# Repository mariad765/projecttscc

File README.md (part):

# projecttscc
date: 2025

# Proiect: OpenBook
Acest proiect utilizează Autodesk Fusion 360 pentru realizarea designului carcasei și a plăcii PCB pentru OpenBook, având la bază microcontrollerul ESP32-C6. Include senzori, module de alimentare și componente conectate prin diverse interfețe.

# Diagrama Bloc

### General:
```
+------------------------+     +------------------------+     +------------------------+
| USB-C + ESD Protection | --> | LDO Voltage Regulator  | --> | Li-Po Charging Ctrl.   |
+------------------------+     +------------------------+     +------------------------+
                                                            |
                                                            v
                                                      +----------------+
                                                      |   Battery      |
                                                      | (3.7V Li-Po)   |
                                                      +----------------+
                                                            |
                                                            v
+------------------+     +------------------+         +-------------------+
| RTC DS3231SN     |<--->|   ESP32-C6       |<------->| E-Paper Display   |
+------------------+     +------------------+         | (Header + Driver) |
                           ^    ^   ^   ^              +-------------------+
                           |    |   |   |
       +------------------+    |   |   +--------------------+
       |                       |   |                        |
       v                       v   v                        v
+--------------+       +--------------+           +----------------------+
| SD Card Slot |       | BME688 Sensor|           | External Flash 64MB  |
+--------------+       +--------------+           +----------------------+
                           ^   |
                           |   v
               +-----------------------------+
               | Voltage Supervisor + Reset  |
               | Boot / IO Button Module     |
               +-----------------------------+

                           ^
                           |
                    +-------------+
                    | EPD Power   |
                    +-------------+

                           ^
                           |
              +-----------------------+
              | SPI ESD Protection    |
              +-----------------------+

                           ^
                           |
            +--------------------------+
            | Qwic / Stemma QT Header |
            +--------------------------+

                           ^
                           |
                     +-----------+
                     | Test Pads |
                     +-----------+

```

### Organizarea componentelor mici:
```

                        +------------------------+
                        | USB-C + ESD Protection |
                        | R1, F1, D1             |
                        +-----------+------------+
                                    |
                                    v
                      +-----------------------------+
                      | LDO Voltage Regulator       |
                      | U4 (XC6220)                 |
                      | D2 (Schottky)               |
                      | C1, C2 (Capacitors)         |
                      +-----------+-----------------+
                                  |
                                  v
          +----------------------------------------------+
          | Li-Po Charging Controller (MCP73831)         |
          | RPROG, C1_BAT, C2_BAT                        |
          +--------------------+-------------------------+
                               |
                               v
                          +---------+
                          | Battery |
                          +---------+

          +------------------------------------------+
          |                ESP32-C6                  |
          | U2, conectat cu GPIO la toate modulele   |
          +--+--------+----------+----------+--------+
             |        |          |          |
             |        |          |          |
             |        |          |          |
             v        v          v          v
+------------------+ +------------------+ +-------------------+ +-------------------+
| RTC DS3231SN     | | BME688 Sensor    | | E-Paper Display   | | External NOR Flash|
| U3, C1, C2       | | Ux, Cx (Filter)  | | Header + Drive    | | U1, Cx (Decouple) |
| + CRYSTAL        | | R (Pull-ups)     | | Q3 (MOSFET),      | |                   |
+------------------+ +------------------+ | L1 (Inductor),    | +-------------------+
                                          | D3, D4 (Diodes)   |
                                          | C3, C4, C5, C6    |
                                          +-------------------+

                      +------------------------------------+
                      | SD Card Module (SPI)              |
                      | + Pull-up Resistors               |
                      +------------------------------------+
                      +--------------------------------------------+
                      | Voltage Supervisor + Boot + Reset Buttons  |
                      | Ux (BD52), R1, R2, C1, C2                   |
                      +--------------------------------------------+
                      +------------------+ +--------------------+
                      | EPD Power        | | SPI ESD Protection |
                      | Zener Diode      | | TVS Diodes         |
                      +------------------+ +--------------------+
                      +---------------------------+
                      | Qwiic / Stemma QT Header  |
                      | 4-Pin Connector           |
                      +---------------------------+

                      +---------------------------+
                      | Test Pads (TP1 - TP17)    |
                      +---------------------------+

```

#### Legenda componente:
R = Rezistențe (pull-up, pull-down, programare)

C = Condensatori (filtrare, decuplare, bypass)

D = Diode (Schottky, Zener, TVS)

Q = Tranzistori (MOSFET, BJT)

L = Bobine (inductoare pentru EPD)

U = Integrate (ESP32-C6, MCP73831, etc.)

TP = Test Pads

CRYSTAL = Oscilator 32.768kHz pentru RTC

<prev>

| **Device**                             | **Datasheet**                                                                                       | **Purchase URL**                                                                                                                                               | **Notes**                                                                                                                                                                                                                                                                                                                |
|----------------------------------------|----------------------------------------------------------------------------------------------------|---------------------------------------------------------------------------------------------------------------------------------------------------------------|--------------------------------------------------------------------------------------------------------------------------------------------------------------------------------------------------------------------------------------------------------------------------------------------------------------------------|
| ADAFRUIT_LEDCHIP-LED0603               | [Datasheet](https://dammedia.osram.info/media/resource/hires/osram-dam-5178061/LH%20R974_EN.pdf)   | [Purchase](https://eu.mouser.com/ProductDetail/ams-OSRAM/LH-R974?qs=rUek3o0zKEvmwAoLLbCfCQ%3D%3D)                                                              |                                                                                                                                                                                                                                                                                                                          |
| ESP32_WROVER_EAGLE-LTSPICE_RR0402      | [Datasheet](https://eu.mouser.com/datasheet/2/447/PYu_RT_1_to_0_01_RoHS_L_15-3461507.pdf)           | [Purchase](https://eu.mouser.com/ProductDetail/YAGEO/RT0402BRE072KL?qs=gY0y7AQI9SOEMRqvTCljCA%3D%3D)                                                           |                                                                                                                                                                                                                                                                                                                          |
| ESP32_WROVER_EAGLE-LTSPICE_RR0402      | [Datasheet](https://eu.mouser.com/datasheet/2/447/PYu_SR_20105_RoHS_L_12-3461462.pdf)               | [Purchase](https://eu.mouser.com/ProductDetail/YAGEO/SR0402FR-0710KL?qs=TyBUSTk9pD%2F02BJ2PplVgA%3D%3D)                                                       |                                                                                                                                                                                                                                                                                                                          |
| EAGLE-LTSPICE_CC0402                   | [Datasheet](https://eu.mouser.com/datasheet/2/447/KEM_C1003_C0G_SMD-3316496.pdf)                    | [Purchase](https://eu.mouser.com/ProductDetail/KEMET/C0402C100J4GACTU?qs=mjekseImwbbdX0mMb15eGA%3D%3D)                                                          |                                                                                                                                                                                                                                                                                                                          |
| SJ                                     | [Datasheet](https://www.snapeda.com/parts/5112/Keystone%20Electronics/datasheet/)                    | [Purchase](https://eu.mouser.com/ProductDetail/Keystone-Electronics/5112?utm_campaign=mouser&qs=u16ybLDytRZh2kbiE9WIqQ==&utm_medium=online&utm_source=snapedaonline&utm_content=datasheet) |                                                                                                                                                                                                                                                                                                                          |
| ESP32_WROVER_EAGLE-LTSPICE_RR0402      | [Datasheet](https://eu.mouser.com/datasheet/2/447/PYu_RC_Group_51_RoHS_L_12-3368608.pdf)            | [Purchase](https://eu.mouser.com/ProductDetail/YAGEO/RC0402FR-07226RL?qs=ZELcmBmapfyYDZKSOq20kw%3D%3D)                                                           |                                                                                                                                                                                                                                                                                                                          |
| EAGLE-LTSPICE_CC0402                   | [Datasheet](https://eu.mouser.com/datasheet/2/447/KEM_C1018_X7R_SnPb_SMD-3316276.pdf)               | [Purchase](https://eu.mouser.com/ProductDetail/KEMET/C0402C104K4RAL?qs=pIZUS6sqCWCaMuP2QVR%2Fog%3D%3D&srsltid=AfmBOorFGwDGmQ6lWmC_Jiog7gZnCk6L84apRuEeDYw4gmpryDUgmfwW)              |                                                                                                                                                                                                                                                                                                                          |
| ESP32_WROVER_EAGLE-LTSPICE_CC0402      | [Datasheet](https://eu.mouser.com/datasheet/2/447/KEM_C1002_X7R_SMD-3316098.pdf)                    | [Purchase](https://eu.mouser.com/ProductDetail/KEMET/C0402C104K4RAC?qs=sykUljcfnH1GXndxGT8AHQ%3D%3D)                                                           |                                                                                                                                                                                                                                                                                                                          |
| RCL_CPOL-EUCT3528                      | [Datasheet](https://www.snapeda.com/parts/OF-SMD3528WC/Optoflash/datasheet/)                          | [Purchase](https://www.tme.eu/en/details/of-smd3528wc/smd-white-leds/optoflash/)                                                                                  |                                                                                                                                                                                                                                                                                                                          |
| ESP32_WROVER_EAGLE-LTSPICE_CC0402      | [Datasheet](https://eu.mouser.com/datasheet/2/447/KEM_C1018_X7R_SnPb_SMD-3316276.pdf)               | [Purchase](https://eu.mouser.com/ProductDetail/KEMET/C0402C104K4RAL?qs=pIZUS6sqCWCaMuP2QVR%2Fog%3D%3D)                                                           |                                                                                                                                                                                                                                                                                                                          |
| 112A-TAAR-R03_ATTEND                   | [Datasheet](https://www.snapeda.com/parts/112A-TAAR-R03/Attend/datasheet/)                            | [Purchase](https://www.tme.eu/ro/details/mcc-sdmicro/conectori-pentru-cartele/attend/112a-taar-r03/)                                                              |                                                                                                                                                                                                                                                                                                                          |
| EAGLE-LTSPICE_CC0402                   | [Datasheet](https://eu.mouser.com/datasheet/2/447/KEM_C1006_X5R_SMD-3316465.pdf)                    | [Purchase](https://eu.mouser.com/ProductDetail/KEMET/C0402C475M9PAC7411?qs=cpo3%2FpBou2jRzZxyxJnMGg%3D%3D)                                                          |                                                                                                                                                                                                                                                                                                                          |
| ESP32_WROVER_SPARKFUN-DISCRETESEMI_MOSFET_PCH-DMG2305UX-7 | [Datasheet](https://www.diodes.com/assets/Datasheets/DMG2305UX.pdf) | [Purchase](https://eu.mouser.com/ProductDetail/Diodes-Incorporated/DMG2305UX-7?qs=L1DZKBg7t5F%2FNBHrjfxC%252Bg%3D%3D) |                                                                                                                                                                                                                                                                                                                          |
| 744043680IND_4828-WE-TPC_WRE           | [Datasheet](https://www.we-online.com/components/products/datasheet/744043680.pdf)                  | [Purchase](https://eu.mouser.com/ProductDetail/Wurth-Elektronik/744043680?qs=PGXP4M47uW6VkZq%252BkzjrHA%3D%3D)                                                    |                                                                                                                                                                                                                                                                                                                          |
| BD5229G-TR                             | [Datasheet](https://fscdn.rohm.com/en/products/databook/datasheet/ic/power/voltage_detector/bd52xxg-e.pdf) | [Purchase](https://eu.mouser.com/ProductDetail/ROHM-Semiconductor/BD5229G-TR?qs=4kLU8WoGk0vvnhrrYwdszw%3D%3D) |                                                                                                                                                                                                                                                                                                                          |
| ESP32_WROVER_BME680_BME680             | [Datasheet](https://eu.mouser.com/datasheet/2/783/bst_bme688_fl000-2307034.pdf)                      | [Purchase](https://eu.mouser.com/ProductDetail/Bosch-Sensortec/BME688?qs=IS%252B4QmGtzzqQoVDscqwx3A%3D%3D)                                                       |                                                                                                                                                                                                                                                                                                                          |
| BUTTON_CUSYOMV1                         | [Datasheet](https://www.ckswitches.com/media/1482/kms.pdf)                                           | [Purchase](https://eu.mouser.com/ProductDetail/CK/KMS231G?qs=cygERTaPE9Aulmq4rq4WXQ%3D%3D)                     | [see note 1]                                                                                      |
| CPH3225A                               | [Datasheet](https://eu.mouser.com/datasheet/2/360/Seiko_Instruments_MicroBattery_E_20230330_2024Jan_-3561061.pdf) | [Purchase](https://eu.mouser.com/ProductDetail/Seiko-Semiconductors/CPH3225A?qs=3etwrb1wR%252BhUOph6lAO7eg%3D%3D&utm_id=6470900573&utm_source=google&utm_medium=cpc&utm_marketing_tactic=emeacorp&gad_source=1&gclid=CjwKCAjwzMi_BhACEiwAX4YZUD6usznTzJWXm4Z9u8rBBFy2NakSyAr25YMlMpxMyBTQ3bVXFg2nFhoCpx0QAvD_BwE) |                                                                                                                                                                                                                                                                                                                          |
| DS3231SN#                              | [Datasheet](https://eu.mouser.com/datasheet/2/609/DS3231-3421123.pdf)                                | [Purchase](https://www.snapeda.com/api/url_track_click_mouser/?unipart_id=562593&manufacturer=Seiko%20Instruments&part_name=CPH3225A&search_term=None)          |                                                                                                                                                                                                                                                                                                                          |
| ESP32-C6-WROOM-1-N8                    | [Datasheet](https://eu.mouser.com/datasheet/2/891/Espressif_ESP32_C6_WROOM_1__Datasheet_V0_1_PRELIMI-3239987.pdf) | [Purchase](https://eu.mouser.com/ProductDetail/Espressif-Systems/ESP32-C6-WROOM-1-N8?qs=8Wlm6%252BaMh8ST02Gmwp74cw%3D%3D)                                            |                                                                                                                                                                                                                                                                                                                          |
| ESP32C6_VARISTORCN1812                 | [Datasheet](https://www.snapeda.com/parts/PFMF.050.2/Schurter/datasheet/)                             | [Purchase](https://www.digikey.com/en/products/detail/schurter-inc/PFMF-050-2/1731348?utm_campaign=buynow&utm_medium=aggregator&utm_source=snapeda)               |                                                                                                                                                                                                                                                                                                                          |
| ESP32_WROVER_AVX---SD0805S020S1R0_AVX_SD0805S020S1R0_0_0AVX_SD0805S020S1R0_0_0 | [Datasheet](http://datasheets.avx.com/schottky.pdf) | [Purchase](https://www.kyocera-avx.com/products/diodes/lead-less-chip-schottky-barrier-diodes/)               |                                                                                                                                                                                                                                                                                                                          |
| ESP32_WROVER_SPARKFUN-IC-POWER_MCP73831 | [Datasheet](https://eu.mouser.com/datasheet/2/268/MCP73831_Family_Data_Sheet_DS20001984H-3441711.pdf) | [Purchase](https://eu.mouser.com/ProductDetail/Microchip-Technology/MCP73831T-2ACI-OT?qs=yUQqVecv4qvbBQBGbHx0Mw%3D%3D)               |                                                                                                                                                                                                                                                                                                                          |
| FH34SRJ-24S-0.5SH_99_                  | [Datasheet](https://www.snapeda.com/parts/FH34SRJ-24S-0.5SH(99)/Hirose%20Electric/datasheet/)         | [Purchase](https://www.digikey.com/en/products/detail/hirose-electric-co-ltd/FH34SRJ-24S-0-5SH-99/5132529?utm_campaign=buynow&utm_medium=aggregator&utm_source=snapeda) |                                                                                                                                                                                                                                                                                                                          |
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
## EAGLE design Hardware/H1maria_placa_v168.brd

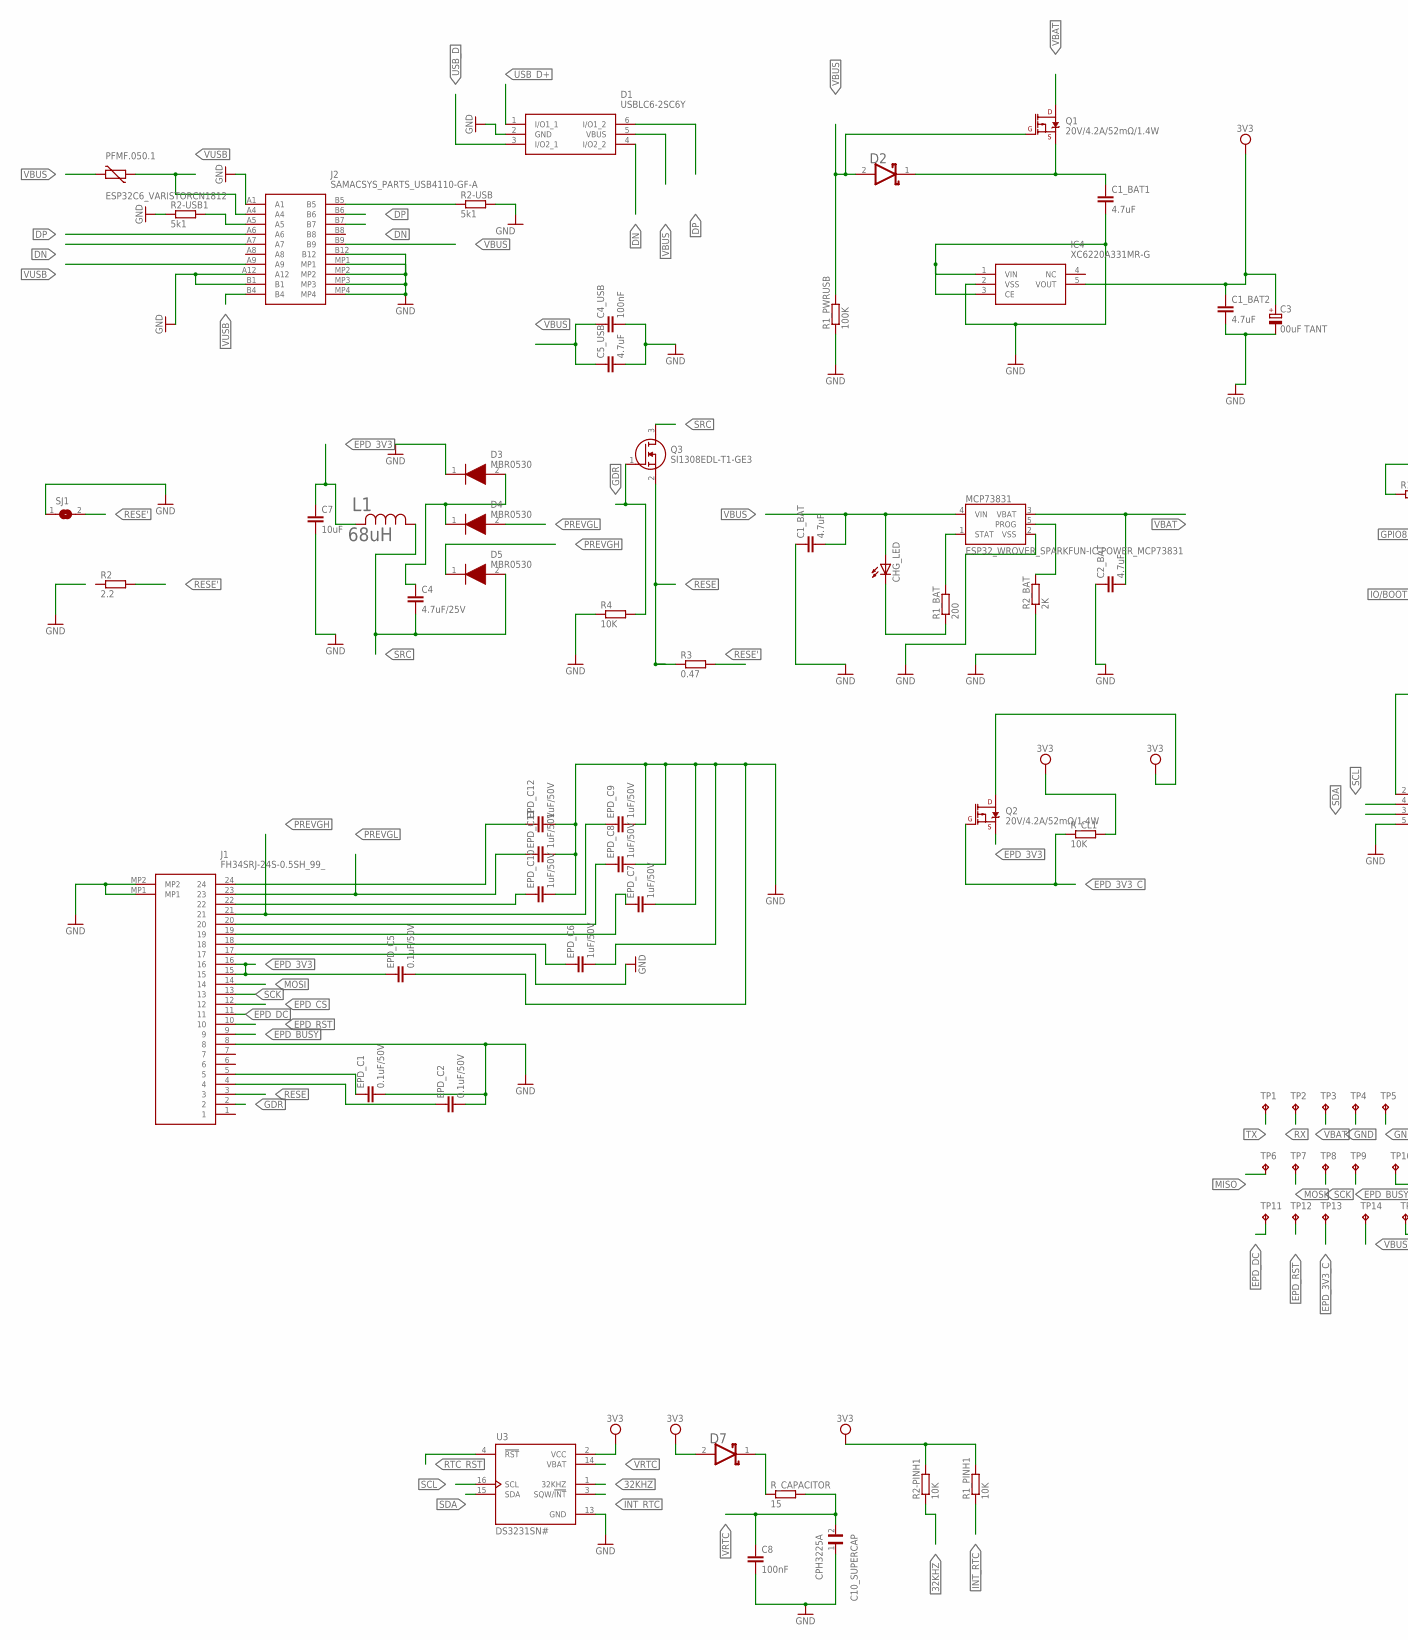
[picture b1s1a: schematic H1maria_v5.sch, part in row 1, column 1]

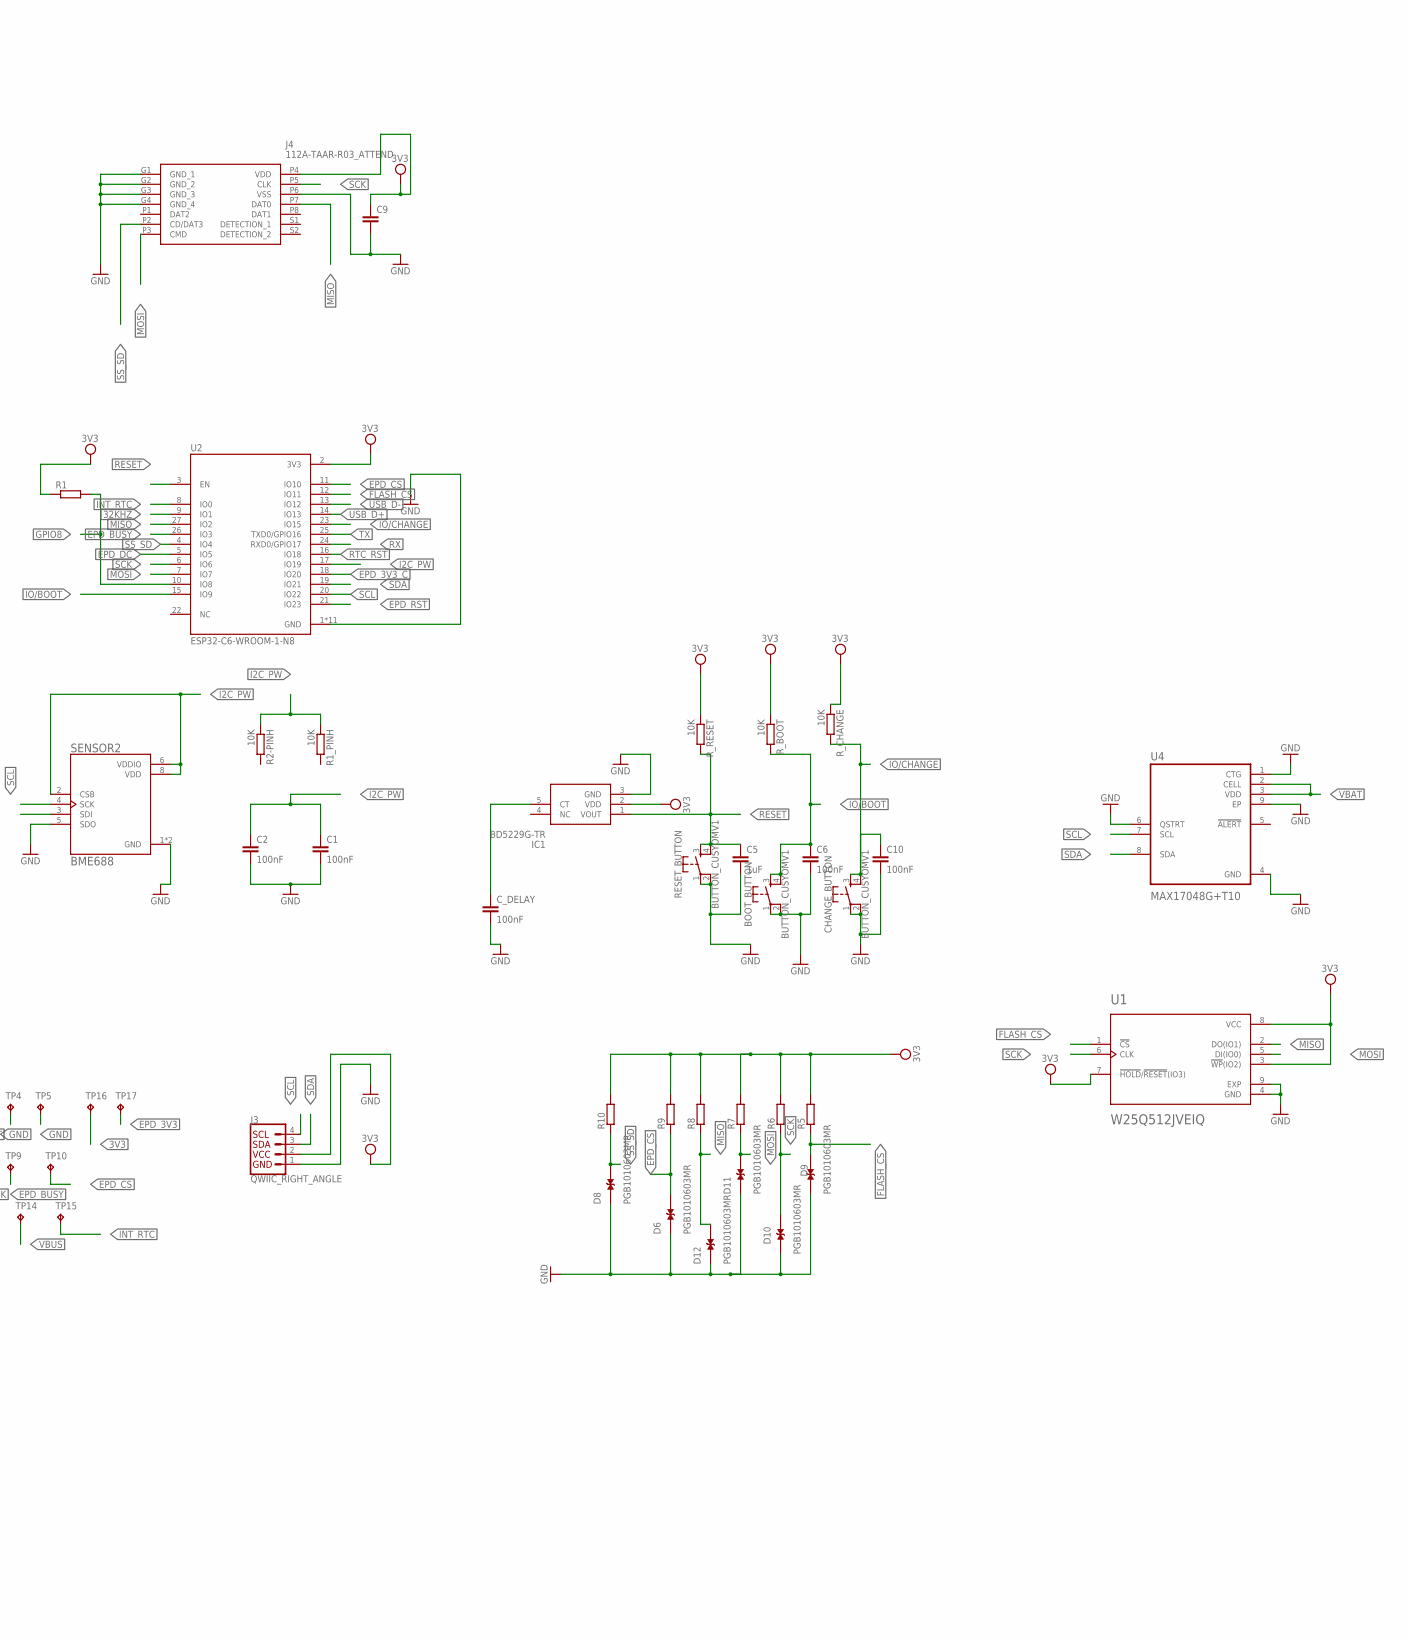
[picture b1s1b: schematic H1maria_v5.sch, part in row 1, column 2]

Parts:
BOOT_BUTTON: BUTTON_CUSYOMV1; MYBUTTON
C1, C2: 100nF; ESP32_WROVER_EAGLE-LTSPICE_C0402
C1_BAT, C1_BAT1, C1_BAT2, C2_BAT, C5_USB: 4.7uF; EAGLE-LTSPICE_C0402
C3: 00uF TANT; RCL_CT3528
C4: 4.7uF/25V; ESP32_WROVER_EAGLE-LTSPICE_C0402
C4_USB, C6, C8, C10: 100nF; EAGLE-LTSPICE_C0402
C5: 1uF; EAGLE-LTSPICE_C0402
C7: 10uF; ESP32_WROVER_EAGLE-LTSPICE_C0402
C9: ESP32_WROVER_EAGLE-LTSPICE_CC0402; ESP32_WROVER_EAGLE-LTSPICE_C0402
C10_SUPERCAP: CPH3225A; CAPCP3225X100N
CHANGE_BUTTON: BUTTON_CUSYOMV1; MYBUTTON
CHG_LED: ADAFRUIT_LEDCHIP-LED0603; ADAFRUIT_CHIP-LED0603
C_DELAY: 100nF; EAGLE-LTSPICE_C0402
D1: USBLC6-2SC6Y; SOT95P280X145-6N
D2: SD0805S020S1R0; ESP32_WROVER_AVX---SD0805S020S1R0_AVX_SD0805S020S1R0_0
D3, D4, D5: MBR0530; SOD3716X135N
D6, D8, D9, D10, D11, D12: PGB1010603MR; DIOC1608X36N
D7: ESP32_WROVER_AVX---SD0805S020S1R0_AVX_SD0805S020S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; ESP32_WROVER_AVX---SD0805S020S1R0_AVX_SD0805S020S1R0_0
EPD_C1, EPD_C2, EPD_C5: 0.1uF/50V; EAGLE-LTSPICE_C0402
EPD_C6, EPD_C7, EPD_C8, EPD_C9, EPD_C10, EPD_C11, EPD_C12: 1uF/50V; EAGLE-LTSPICE_C0402
IC1: BD5229G-TR; SOT95P280X125-5N
IC4: XC6220A331MR-G; SOT95P280X120-5N
J1: FH34SRJ-24S-0.5SH_99_; FH34SRJ24S05SH99
J2: SAMACSYS_PARTS_USB4110-GF-A; SAMACSYS_PARTS_USB4110GFA
J3: QWIIC_RIGHT_ANGLE; JST04_1MM_RA
J4: 112A-TAAR-R03_ATTEND; 112ATAARR03ATTEND
L1: 68uH; IND_4828-WE-TPC_WRE
MCP73831: ESP32_WROVER_SPARKFUN-IC-POWER_MCP73831; ESP32_WROVER_SPARKFUN-IC-POWER_SOT23-5
PFMF.050.1: ESP32C6_VARISTORCN1812; ESP32C6_VARISTOR_CT/CN1812
Q1, Q2: 20V/4.2A/52mΩ/1.4W; ESP32_WROVER_SPARKFUN-DISCRETESEMI_SOT23-3
Q3: SI1308EDL-T1-GE3; SOT65P210X110-3N
R1, R5, R6, R7, R8, R9, R10: ESP32_WROVER_EAGLE-LTSPICE_RR0402; ESP32_WROVER_EAGLE-LTSPICE_R0402
R1_BAT: 200; ESP32_WROVER_EAGLE-LTSPICE_R0402
R1_PINH, R1_PINH1, R2-PINH, R2-PINH1, R4: 10K; ESP32_WROVER_EAGLE-LTSPICE_R0402
R1_PWRUSB: 100K; ESP32_WROVER_EAGLE-LTSPICE_R0402
R2: 2.2; ESP32_WROVER_EAGLE-LTSPICE_R0402
R2-USB, R2-USB1: 5k1; ESP32_WROVER_EAGLE-LTSPICE_R0402
R2_BAT: 2K; ESP32_WROVER_EAGLE-LTSPICE_R0402
R3: 0.47; ESP32_WROVER_EAGLE-LTSPICE_R0402
RESET_BUTTON: BUTTON_CUSYOMV1; MYBUTTON
R_BOOT: 10K; ESP32_WROVER_EAGLE-LTSPICE_R0402
R_CAPACITOR: 15; ESP32_WROVER_EAGLE-LTSPICE_R0402
R_CHANGE: 10K; ESP32_WROVER_EAGLE-LTSPICE_R0402
R_CL1: 10K; ESP32_WROVER_EAGLE-LTSPICE_R0402
R_RESET: 10K; ESP32_WROVER_EAGLE-LTSPICE_R0402
SENSOR2: BME688; ESP32_WROVER_BME680_PSON80P300X300X100-8N
SJ1: SJ
TP1, TP2, TP3, TP4, TP5, TP6, TP7, TP8, TP9, TP10, TP11, TP12, TP13, TP14, TP15, TP16, TP17: TPTP20R; TP20R
U1: W25Q512JVEIQ; SON127P600X800X80-9N
U2: ESP32-C6-WROOM-1-N8; XCVR_ESP32-C6-WROOM-1-N8
U3: DS3231SN#; SOIC127P1032X265-16N
U4: MAX17048G+T10; SON50P200X200X80-9N

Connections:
3V3: C1_BAT2.1, C3.+, C9.1, D7.2 (ANODE), IC1.2 (VDD), IC4.5 (VOUT), J3.2, J4.P4 (VDD), Q2.3 (D), R1.1, R1_PINH1.2, R2-PINH1.2, R5.2, R6.2, R7.2, R8.2, R9.2, R10.2, R_BOOT.1, R_CHANGE.1, R_CL1.2, R_RESET.1, TP16.TP, U1.3 (!WP!(IO2)), U1.7 (!HOLD!/!RESET!(IO3)), U1.8 (VCC), U2.2 (3V3), U3.2 (VCC)
32KHZ: R2-PINH1.1, U2.9 (IO1), U3.1 (32KHZ)
DN: D1.4 (I/O2_2), J2.A7, J2.B7
DP: D1.6 (I/O1_2), J2.A6, J2.B6
EPD_3V3: C7.1, EPD_C5.1, J1.15, J1.16, L1.2, Q2.2 (S), TP17.TP
EPD_3V3_C: Q2.1 (G), R_CL1.1, TP13.TP, U2.18 (IO20)
EPD_BUSY: J1.9, TP9.TP, U2.26 (IO3)
EPD_CS: D6.2, J1.12, R9.1, TP10.TP, U2.11 (IO10)
EPD_DC: J1.11, TP11.TP, U2.5 (IO5)
EPD_RST: J1.10, TP12.TP, U2.21 (IO23)
FLASH_CS: D9.2, R5.1, U1.1 (!CS), U2.12 (IO11)
GDR: J1.2, Q3.1 (G), R4.2
GND: BOOT_BUTTON.1, BOOT_BUTTON.2, C1.2, C1_BAT.1, C1_BAT1.2, C1_BAT2.2, C2.2, C2_BAT.1, C3.-, C4_USB.2, C5.2, C5_USB.2, C6.2, C7.2, C8.2, C9.2, C10.2, C10_SUPERCAP.1, CHANGE_BUTTON.1, CHANGE_BUTTON.2, C_DELAY.2, D1.2 (GND), D3.1 (K), D6.1, D8.1, D9.1, D10.1, D11.1, D12.1, EPD_C1.2, EPD_C2.2, EPD_C5.2, EPD_C6.2, EPD_C7.2, EPD_C8.2, EPD_C9.2, EPD_C10.2, EPD_C11.2, EPD_C12.2, IC1.3 (GND), IC4.1 (VIN), IC4.2 (VSS), IC4.3 (CE), J1.8, J1.17, J1.MP1, J1.MP2, J2.A1, J2.A12, J2.B1, J2.B12, J2.MP1, J2.MP2, J2.MP3, J2.MP4, J3.1, J4.G1 (GND_1), J4.G2 (GND_2), J4.G3 (GND_3), J4.G4 (GND_4), J4.P6 (VSS), MCP73831.2 (VSS), R1_PWRUSB.1, R2-USB.2, R2-USB1.1, R2_BAT.1, R4.1, RESET_BUTTON.1, RESET_BUTTON.2, SENSOR2.1 (GND), SENSOR2.5 (SDO), SENSOR2.7 (GND), SJ1.1, TP4.TP, TP5.TP, U1.4 (GND), U1.9 (EXP), U2.1 (GND), U2.28 (GND), U2.29_1 (GND), U2.29_2 (GND), U2.29_3 (GND), U2.29_4 (GND), U2.29_5 (GND), U2.29_6 (GND), U2.29_7 (GND), U2.29_8 (GND), U2.29_9 (GND), U3.13 (GND), U4.1 (CTG), U4.4 (GND), U4.6 (QSTRT), U4.9 (EP); also elsewhere on the board
GPIO8: R1.2, U2.10 (IO8)
I2C_PW: C1.1, C2.1, R1_PINH.1, R2-PINH.1, SENSOR2.2 (CSB), SENSOR2.6 (VDDIO), SENSOR2.8 (VDD), U2.17 (IO19)
INT_RTC: R1_PINH1.1, TP15.TP, U2.8 (IO0), U3.3 (SQW/!INT)
IO/BOOT: BOOT_BUTTON.3, BOOT_BUTTON.4, C6.1, R_BOOT.2, U2.15 (IO9)
IO/CHANGE: C10.1, CHANGE_BUTTON.3, CHANGE_BUTTON.4, R_CHANGE.2, U2.23 (IO15)
MISO: D12.2, J4.P7 (DAT0), R8.1, TP6.TP, U1.2 (DO(IO1)), U2.27 (IO2)
MOSI: D11.2, J1.14, J4.P3 (CMD), R7.1, TP7.TP, U1.5 (DI(IO0)), U2.7 (IO7)
unnamed: J2.A5, R2-USB1.2
unnamed: J2.B5, R2-USB.1
unnamed: C1_BAT1.1, D2.1 (CATHODE), Q1.2 (S)
unnamed: C4.1, D3.2 (A), D4.1 (K)
unnamed: CHG_LED.C, R1_BAT.1
unnamed: MCP73831.1 (STAT), R1_BAT.2
unnamed: MCP73831.5 (PROG), R2_BAT.2
unnamed: EPD_C12.1, J1.24
unnamed: EPD_C1.1, J1.5
unnamed: EPD_C10.1, J1.22
unnamed: EPD_C2.1, J1.4
unnamed: EPD_C8.1, J1.20
unnamed: EPD_C7.1, J1.19
unnamed: EPD_C6.1, J1.18
unnamed: C_DELAY.1, IC1.5 (CT)
unnamed: D7.1 (CATHODE), R_CAPACITOR.1
PREVGH: D5.1 (K), EPD_C9.1, J1.21
PREVGL: D4.2 (A), EPD_C11.1, J1.23
RESE: J1.3, Q3.2 (S), R3.1
RESE': R2.2, R3.2, SJ1.2
RESET: C5.1, IC1.1 (VOUT), RESET_BUTTON.3, RESET_BUTTON.4, R_RESET.2, U2.3 (EN)
RTC_RST: U2.16 (IO18), U3.4 (!RST)
RX: TP2.TP, U2.24 (RXD0/GPIO17)
SCK: D10.2, J1.13, J4.P5 (CLK), R6.1, TP8.TP, U1.6 (CLK), U2.6 (IO6)
SCL: J3.4, SENSOR2.4 (SCK), U2.20 (IO22), U3.16 (SCL), U4.7 (SCL); also elsewhere on the board
SDA: J3.3, SENSOR2.3 (SDI), U2.19 (IO21), U3.15 (SDA), U4.8 (SDA); also elsewhere on the board
SRC: C4.2, D5.2 (A), L1.1, Q3.3 (D)
SS_SD: D8.2, J4.P2 (CD/DAT3), R10.1, U2.4 (IO4)
TX: TP1.TP, U2.25 (TXD0/GPIO16)
USB_D: D1.3 (I/O2_1)
USB_D+: D1.1 (I/O1_1), U2.14 (IO13)
USB_D-: U2.13 (IO12)
VBAT: C2_BAT.2, MCP73831.3 (VBAT), Q1.3 (D), TP3.TP, U4.2 (CELL), U4.3 (VDD)
VBUS: C1_BAT.2, C4_USB.1, C5_USB.1, CHG_LED.A, D1.5 (VBUS), D2.2 (ANODE), J2.B9, MCP73831.4 (VIN), PFMF.050.1.2, Q1.1 (G), R1_PWRUSB.2, TP14.TP
VRTC: C8.1, C10_SUPERCAP.2, R_CAPACITOR.2, U3.14 (VBAT)
VUSB: J2.A4, J2.A9, J2.B4, PFMF.050.1.1

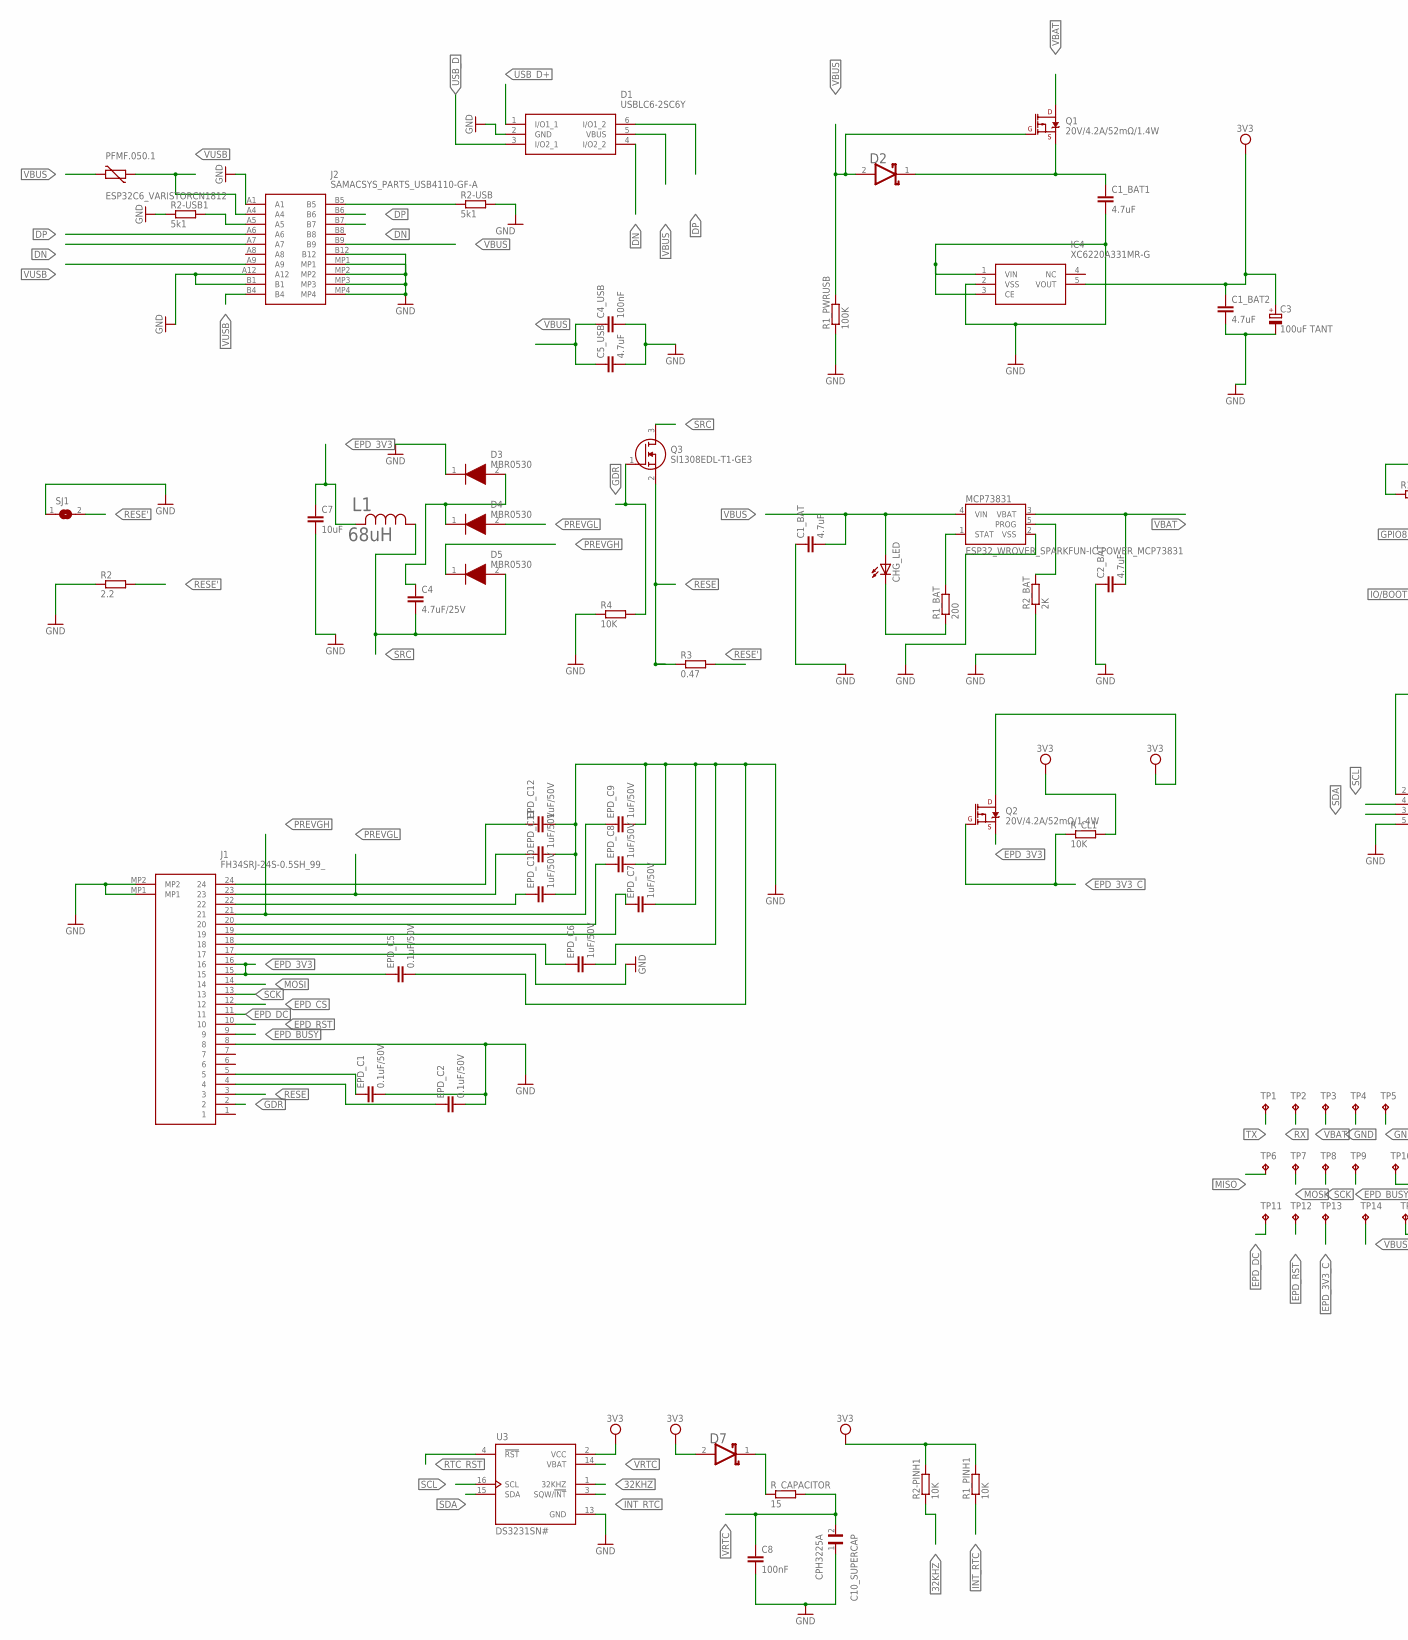
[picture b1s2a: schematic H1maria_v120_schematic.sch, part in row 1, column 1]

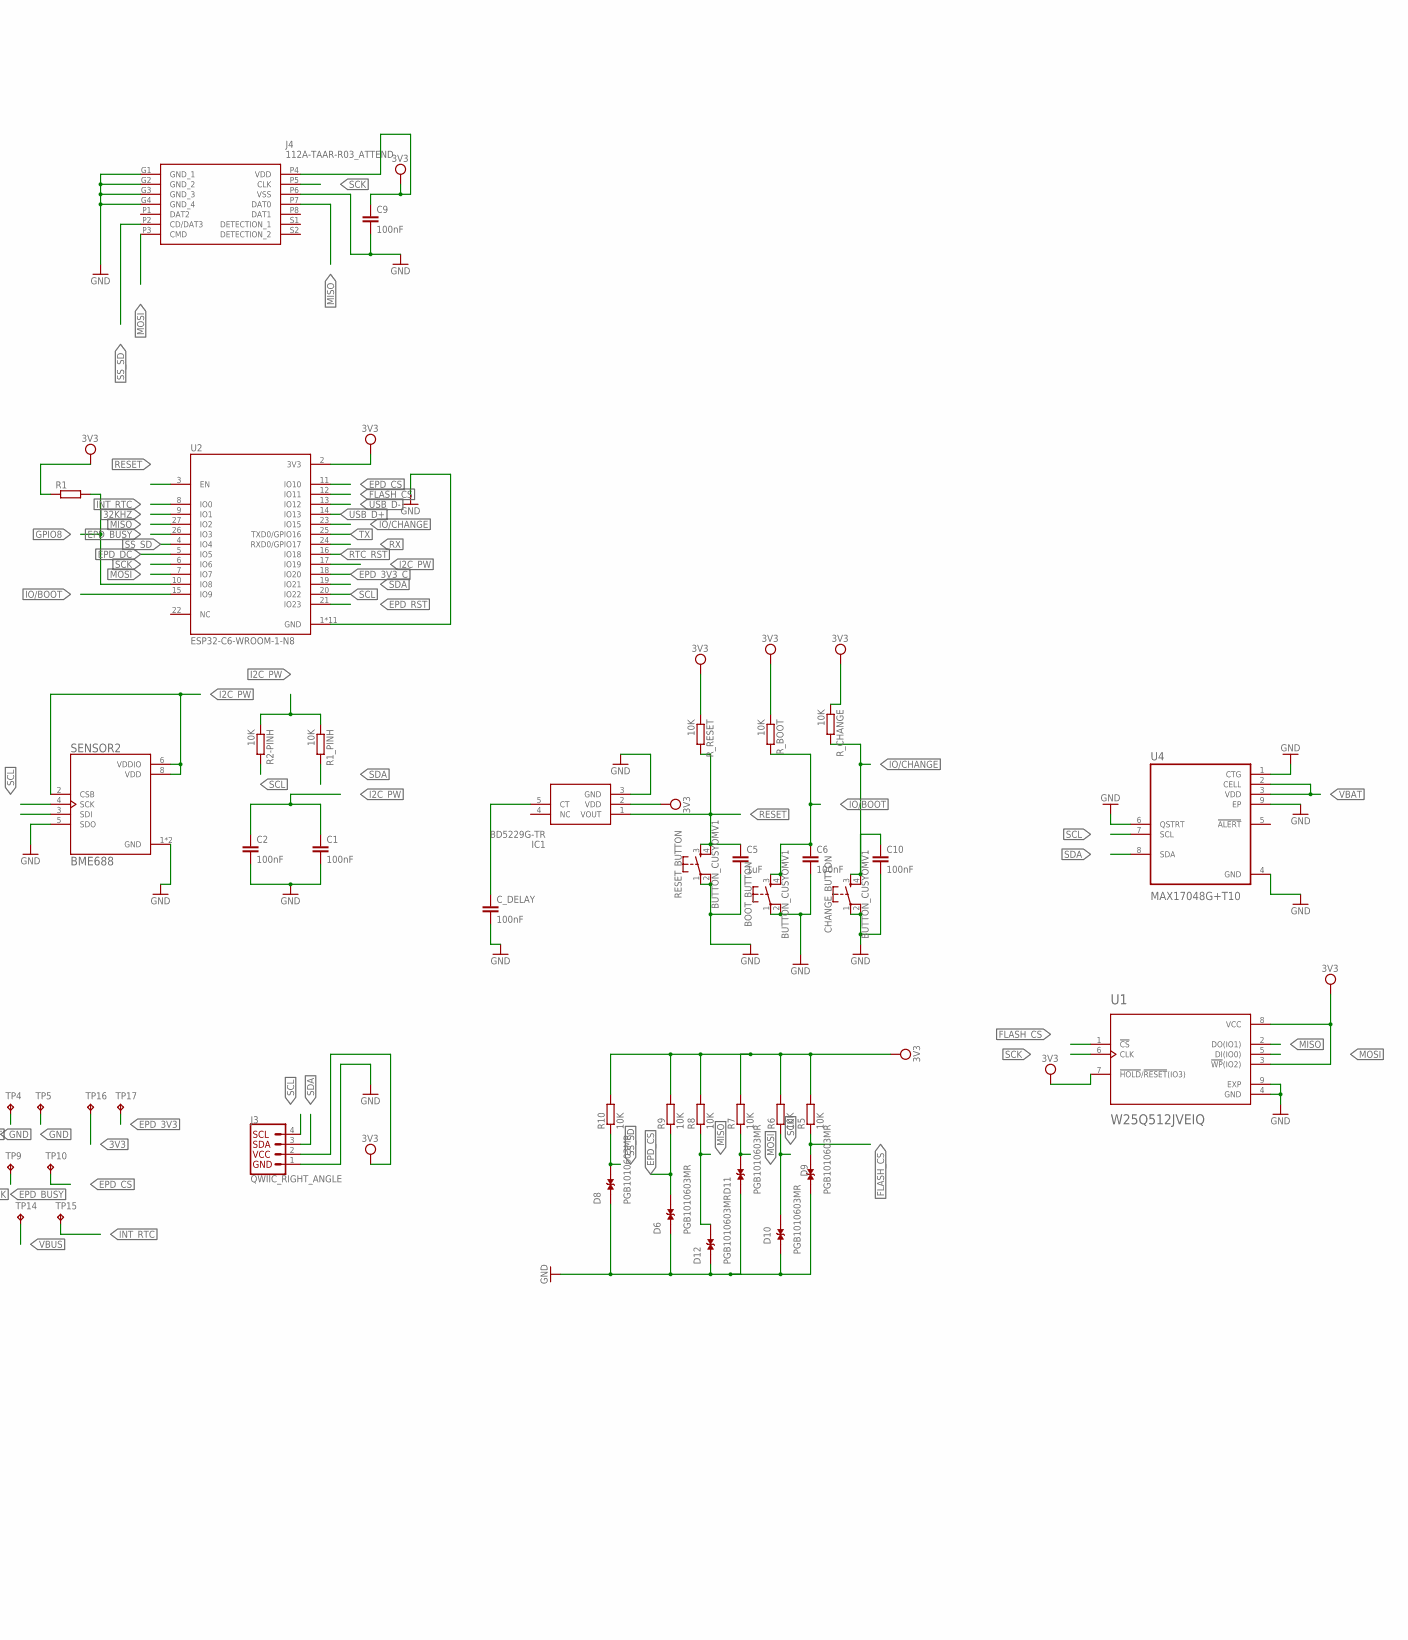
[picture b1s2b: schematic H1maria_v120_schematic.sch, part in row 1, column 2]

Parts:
BOOT_BUTTON: BUTTON_CUSYOMV1; MYBUTTON
C1, C2, C9: 100nF; ESP32_WROVER_EAGLE-LTSPICE_C0402
C1_BAT, C1_BAT1, C1_BAT2, C2_BAT, C5_USB: 4.7uF; EAGLE-LTSPICE_C0402
C3: 100uF TANT; RCL_CT3528
C4: 4.7uF/25V; ESP32_WROVER_EAGLE-LTSPICE_C0402
C4_USB, C6, C8, C10: 100nF; EAGLE-LTSPICE_C0402
C5: 1uF; EAGLE-LTSPICE_C0402
C7: 10uF; ESP32_WROVER_EAGLE-LTSPICE_C0402
C10_SUPERCAP: CPH3225A; CAPCP3225X100N
CHANGE_BUTTON: BUTTON_CUSYOMV1; MYBUTTON
CHG_LED: ADAFRUIT_LEDCHIP-LED0603; ADAFRUIT_CHIP-LED0603
C_DELAY: 100nF; EAGLE-LTSPICE_C0402
D1: USBLC6-2SC6Y; SOT95P280X145-6N
D2: SD0805S020S1R0; ESP32_WROVER_AVX---SD0805S020S1R0_AVX_SD0805S020S1R0_0
D3, D4, D5: MBR0530; SOD3716X135N
D6, D8, D9, D10, D11, D12: PGB1010603MR; DIOC1608X36N
D7: ESP32_WROVER_AVX---SD0805S020S1R0_AVX_SD0805S020S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; ESP32_WROVER_AVX---SD0805S020S1R0_AVX_SD0805S020S1R0_0
EPD_C1, EPD_C2, EPD_C5: 0.1uF/50V; EAGLE-LTSPICE_C0402
EPD_C6, EPD_C7, EPD_C8, EPD_C9, EPD_C10, EPD_C11, EPD_C12: 1uF/50V; EAGLE-LTSPICE_C0402
IC1: BD5229G-TR; SOT95P280X125-5N
IC4: XC6220A331MR-G; SOT95P280X120-5N
J1: FH34SRJ-24S-0.5SH_99_; FH34SRJ24S05SH99
J2: SAMACSYS_PARTS_USB4110-GF-A; SAMACSYS_PARTS_USB4110GFA
J3: QWIIC_RIGHT_ANGLE; JST04_1MM_RA
J4: 112A-TAAR-R03_ATTEND; 112ATAARR03ATTEND
L1: 68uH; IND_4828-WE-TPC_WRE
MCP73831: ESP32_WROVER_SPARKFUN-IC-POWER_MCP73831; ESP32_WROVER_SPARKFUN-IC-POWER_SOT23-5
PFMF.050.1: ESP32C6_VARISTORCN1812; ESP32C6_VARISTOR_CT/CN1812
Q1, Q2: 20V/4.2A/52mΩ/1.4W; ESP32_WROVER_SPARKFUN-DISCRETESEMI_SOT23-3
Q3: SI1308EDL-T1-GE3; SOT65P210X110-3N
R1: ESP32_WROVER_EAGLE-LTSPICE_RR0402; ESP32_WROVER_EAGLE-LTSPICE_R0402
R1_BAT: 200; ESP32_WROVER_EAGLE-LTSPICE_R0402
R1_PINH, R1_PINH1, R2-PINH, R2-PINH1, R4, R5, R6, R7, R8, R9, R10: 10K; ESP32_WROVER_EAGLE-LTSPICE_R0402
R1_PWRUSB: 100K; ESP32_WROVER_EAGLE-LTSPICE_R0402
R2: 2.2; ESP32_WROVER_EAGLE-LTSPICE_R0402
R2-USB, R2-USB1: 5k1; ESP32_WROVER_EAGLE-LTSPICE_R0402
R2_BAT: 2K; ESP32_WROVER_EAGLE-LTSPICE_R0402
R3: 0.47; ESP32_WROVER_EAGLE-LTSPICE_R0402
RESET_BUTTON: BUTTON_CUSYOMV1; MYBUTTON
R_BOOT: 10K; ESP32_WROVER_EAGLE-LTSPICE_R0402
R_CAPACITOR: 15; ESP32_WROVER_EAGLE-LTSPICE_R0402
R_CHANGE: 10K; ESP32_WROVER_EAGLE-LTSPICE_R0402
R_CL1: 10K; ESP32_WROVER_EAGLE-LTSPICE_R0402
R_RESET: 10K; ESP32_WROVER_EAGLE-LTSPICE_R0402
SENSOR2: BME688; ESP32_WROVER_BME680_PSON80P300X300X100-8N
SJ1: SJ
TP1, TP2, TP3, TP4, TP5, TP6, TP7, TP8, TP9, TP10, TP11, TP12, TP13, TP14, TP15, TP16, TP17: TPTP20R; TP20R
U1: W25Q512JVEIQ; SON127P600X800X80-9N
U2: ESP32-C6-WROOM-1-N8; XCVR_ESP32-C6-WROOM-1-N8
U3: DS3231SN#; SOIC127P1032X265-16N
U4: MAX17048G+T10; SON50P200X200X80-9N

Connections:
3V3: C1_BAT2.1, C3.+, C9.1, D7.2 (ANODE), IC1.2 (VDD), IC4.5 (VOUT), J3.2, J4.P4 (VDD), Q2.3 (D), R1.1, R1_PINH1.2, R2-PINH1.2, R5.2, R6.2, R7.2, R8.2, R9.2, R10.2, R_BOOT.1, R_CHANGE.1, R_CL1.2, R_RESET.1, TP16.TP, U1.3 (!WP!(IO2)), U1.7 (!HOLD!/!RESET!(IO3)), U1.8 (VCC), U2.2 (3V3), U3.2 (VCC)
32KHZ: R2-PINH1.1, U2.9 (IO1), U3.1 (32KHZ)
DN: D1.4 (I/O2_2), J2.A7, J2.B7
DP: D1.6 (I/O1_2), J2.A6, J2.B6
EPD_3V3: C7.1, EPD_C5.1, J1.15, J1.16, L1.2, Q2.2 (S), TP17.TP
EPD_3V3_C: Q2.1 (G), R_CL1.1, TP13.TP, U2.18 (IO20)
EPD_BUSY: J1.9, TP9.TP, U2.26 (IO3)
EPD_CS: D6.2, J1.12, R9.1, TP10.TP, U2.11 (IO10)
EPD_DC: J1.11, TP11.TP, U2.5 (IO5)
EPD_RST: J1.10, TP12.TP, U2.21 (IO23)
FLASH_CS: D9.2, R5.1, U1.1 (!CS), U2.12 (IO11)
GDR: J1.2, Q3.1 (G), R4.2
GND: BOOT_BUTTON.1, BOOT_BUTTON.2, C1.2, C1_BAT.1, C1_BAT1.2, C1_BAT2.2, C2.2, C2_BAT.1, C3.-, C4_USB.2, C5.2, C5_USB.2, C6.2, C7.2, C8.2, C9.2, C10.2, C10_SUPERCAP.1, CHANGE_BUTTON.1, CHANGE_BUTTON.2, C_DELAY.2, D1.2 (GND), D3.1 (K), D6.1, D8.1, D9.1, D10.1, D11.1, D12.1, EPD_C1.2, EPD_C2.2, EPD_C5.2, EPD_C6.2, EPD_C7.2, EPD_C8.2, EPD_C9.2, EPD_C10.2, EPD_C11.2, EPD_C12.2, IC1.3 (GND), IC4.1 (VIN), IC4.2 (VSS), IC4.3 (CE), J1.8, J1.17, J1.MP1, J1.MP2, J2.A1, J2.A12, J2.B1, J2.B12, J2.MP1, J2.MP2, J2.MP3, J2.MP4, J3.1, J4.G1 (GND_1), J4.G2 (GND_2), J4.G3 (GND_3), J4.G4 (GND_4), J4.P6 (VSS), MCP73831.2 (VSS), R1_PWRUSB.1, R2.1, R2-USB.2, R2-USB1.1, R2_BAT.1, R4.1, RESET_BUTTON.1, RESET_BUTTON.2, SENSOR2.1 (GND), SENSOR2.5 (SDO), SENSOR2.7 (GND), SJ1.1, TP4.TP, TP5.TP, U1.4 (GND), U1.9 (EXP), U2.1 (GND), U2.28 (GND), U2.29_1 (GND), U2.29_2 (GND), U2.29_3 (GND), U2.29_4 (GND), U2.29_5 (GND), U2.29_6 (GND), U2.29_7 (GND), U2.29_8 (GND), U2.29_9 (GND), U3.13 (GND), U4.1 (CTG), U4.4 (GND), U4.6 (QSTRT), U4.9 (EP)
GPIO8: R1.2, U2.10 (IO8)
I2C_PW: C1.1, C2.1, R1_PINH.1, R2-PINH.1, SENSOR2.2 (CSB), SENSOR2.6 (VDDIO), SENSOR2.8 (VDD), U2.17 (IO19)
INT_RTC: R1_PINH1.1, TP15.TP, U2.8 (IO0), U3.3 (SQW/!INT)
IO/BOOT: BOOT_BUTTON.3, BOOT_BUTTON.4, C6.1, R_BOOT.2, U2.15 (IO9)
IO/CHANGE: C10.1, CHANGE_BUTTON.3, CHANGE_BUTTON.4, R_CHANGE.2, U2.23 (IO15)
MISO: D12.2, J4.P7 (DAT0), R8.1, TP6.TP, U1.2 (DO(IO1)), U2.27 (IO2)
MOSI: D11.2, J1.14, J4.P3 (CMD), R7.1, TP7.TP, U1.5 (DI(IO0)), U2.7 (IO7)
unnamed: J2.A5, R2-USB1.2
unnamed: J2.B5, R2-USB.1
unnamed: C1_BAT1.1, D2.1 (CATHODE), Q1.2 (S)
unnamed: C4.1, D3.2 (A), D4.1 (K)
unnamed: CHG_LED.C, R1_BAT.1
unnamed: MCP73831.1 (STAT), R1_BAT.2
unnamed: MCP73831.5 (PROG), R2_BAT.2
unnamed: EPD_C12.1, J1.24
unnamed: EPD_C1.1, J1.5
unnamed: EPD_C10.1, J1.22
unnamed: EPD_C2.1, J1.4
unnamed: EPD_C8.1, J1.20
unnamed: EPD_C7.1, J1.19
unnamed: EPD_C6.1, J1.18
unnamed: C_DELAY.1, IC1.5 (CT)
unnamed: D7.1 (CATHODE), R_CAPACITOR.1
PREVGH: D5.1 (K), EPD_C9.1, J1.21
PREVGL: D4.2 (A), EPD_C11.1, J1.23
RESE: J1.3, Q3.2 (S), R3.1
RESE': R2.2, R3.2, SJ1.2
RESET: C5.1, IC1.1 (VOUT), RESET_BUTTON.3, RESET_BUTTON.4, R_RESET.2, U2.3 (EN)
RTC_RST: U2.16 (IO18), U3.4 (!RST)
RX: TP2.TP, U2.24 (RXD0/GPIO17)
SCK: D10.2, J1.13, J4.P5 (CLK), R6.1, TP8.TP, U1.6 (CLK), U2.6 (IO6)
SCL: J3.4, R2-PINH.2, SENSOR2.4 (SCK), U2.20 (IO22), U3.16 (SCL), U4.7 (SCL)
SDA: J3.3, R1_PINH.2, SENSOR2.3 (SDI), U2.19 (IO21), U3.15 (SDA), U4.8 (SDA)
SRC: C4.2, D5.2 (A), L1.1, Q3.3 (D)
SS_SD: D8.2, J4.P2 (CD/DAT3), R10.1, U2.4 (IO4)
TX: TP1.TP, U2.25 (TXD0/GPIO16)
USB_D: D1.3 (I/O2_1)
USB_D+: D1.1 (I/O1_1), U2.14 (IO13)
USB_D-: U2.13 (IO12)
VBAT: C2_BAT.2, MCP73831.3 (VBAT), Q1.3 (D), TP3.TP, U4.2 (CELL), U4.3 (VDD)
VBUS: C1_BAT.2, C4_USB.1, C5_USB.1, CHG_LED.A, D1.5 (VBUS), D2.2 (ANODE), J2.B9, MCP73831.4 (VIN), PFMF.050.1.2, Q1.1 (G), R1_PWRUSB.2, TP14.TP
VRTC: C8.1, C10_SUPERCAP.2, R_CAPACITOR.2, U3.14 (VBAT)
VUSB: J2.A4, J2.A9, J2.B4, PFMF.050.1.1

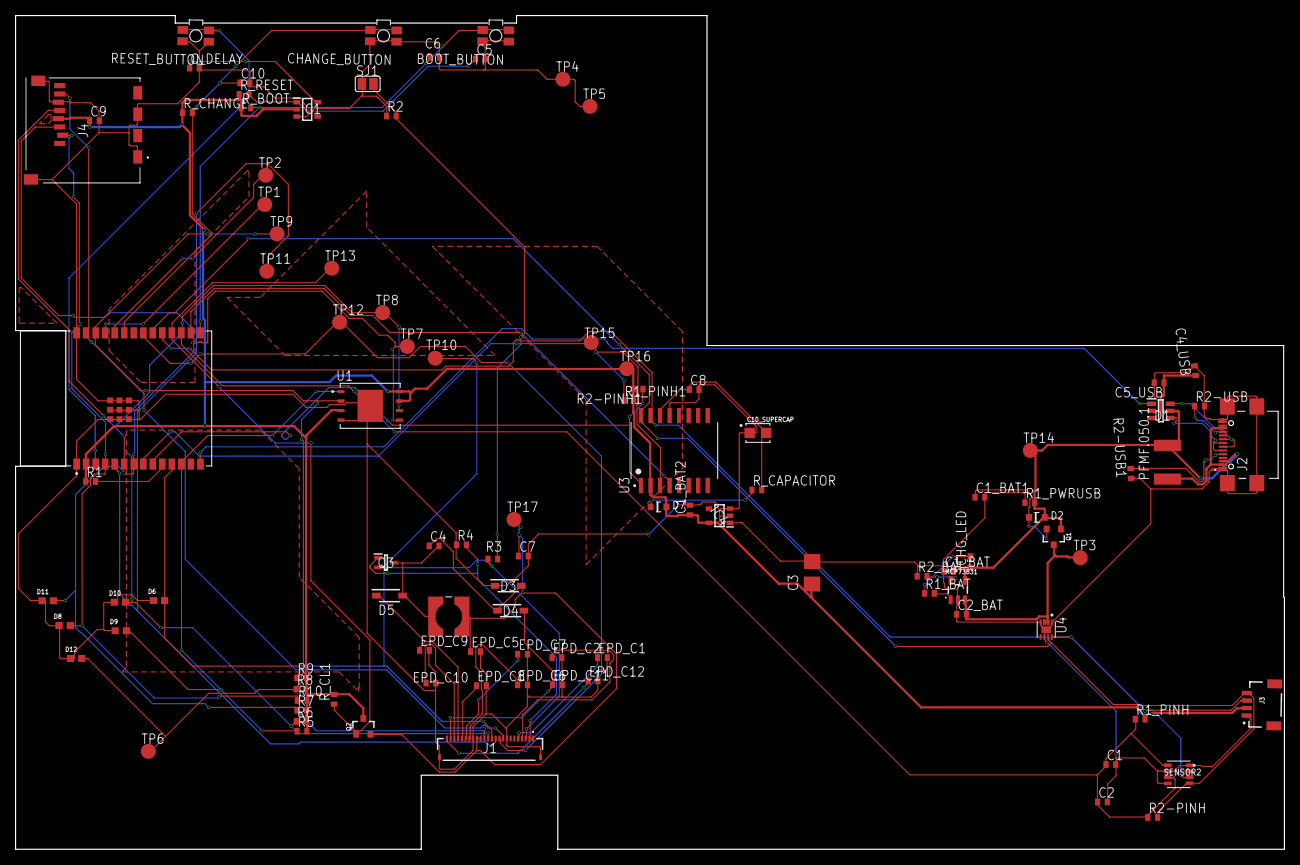
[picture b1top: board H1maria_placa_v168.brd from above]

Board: 2 copper layers, 169.2 x 111.2 mm, 103 parts (0 on the bottom side), 54 nets.

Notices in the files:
README.md:
Distribuit sub licența GNU GPL v3. Pentru detalii, consultă fișierul LICENSE din acest repository.
parts and their libraries:
COPYRIGHT: Copyright (C) 2024 Ultra Librarian. All rights reserved.
